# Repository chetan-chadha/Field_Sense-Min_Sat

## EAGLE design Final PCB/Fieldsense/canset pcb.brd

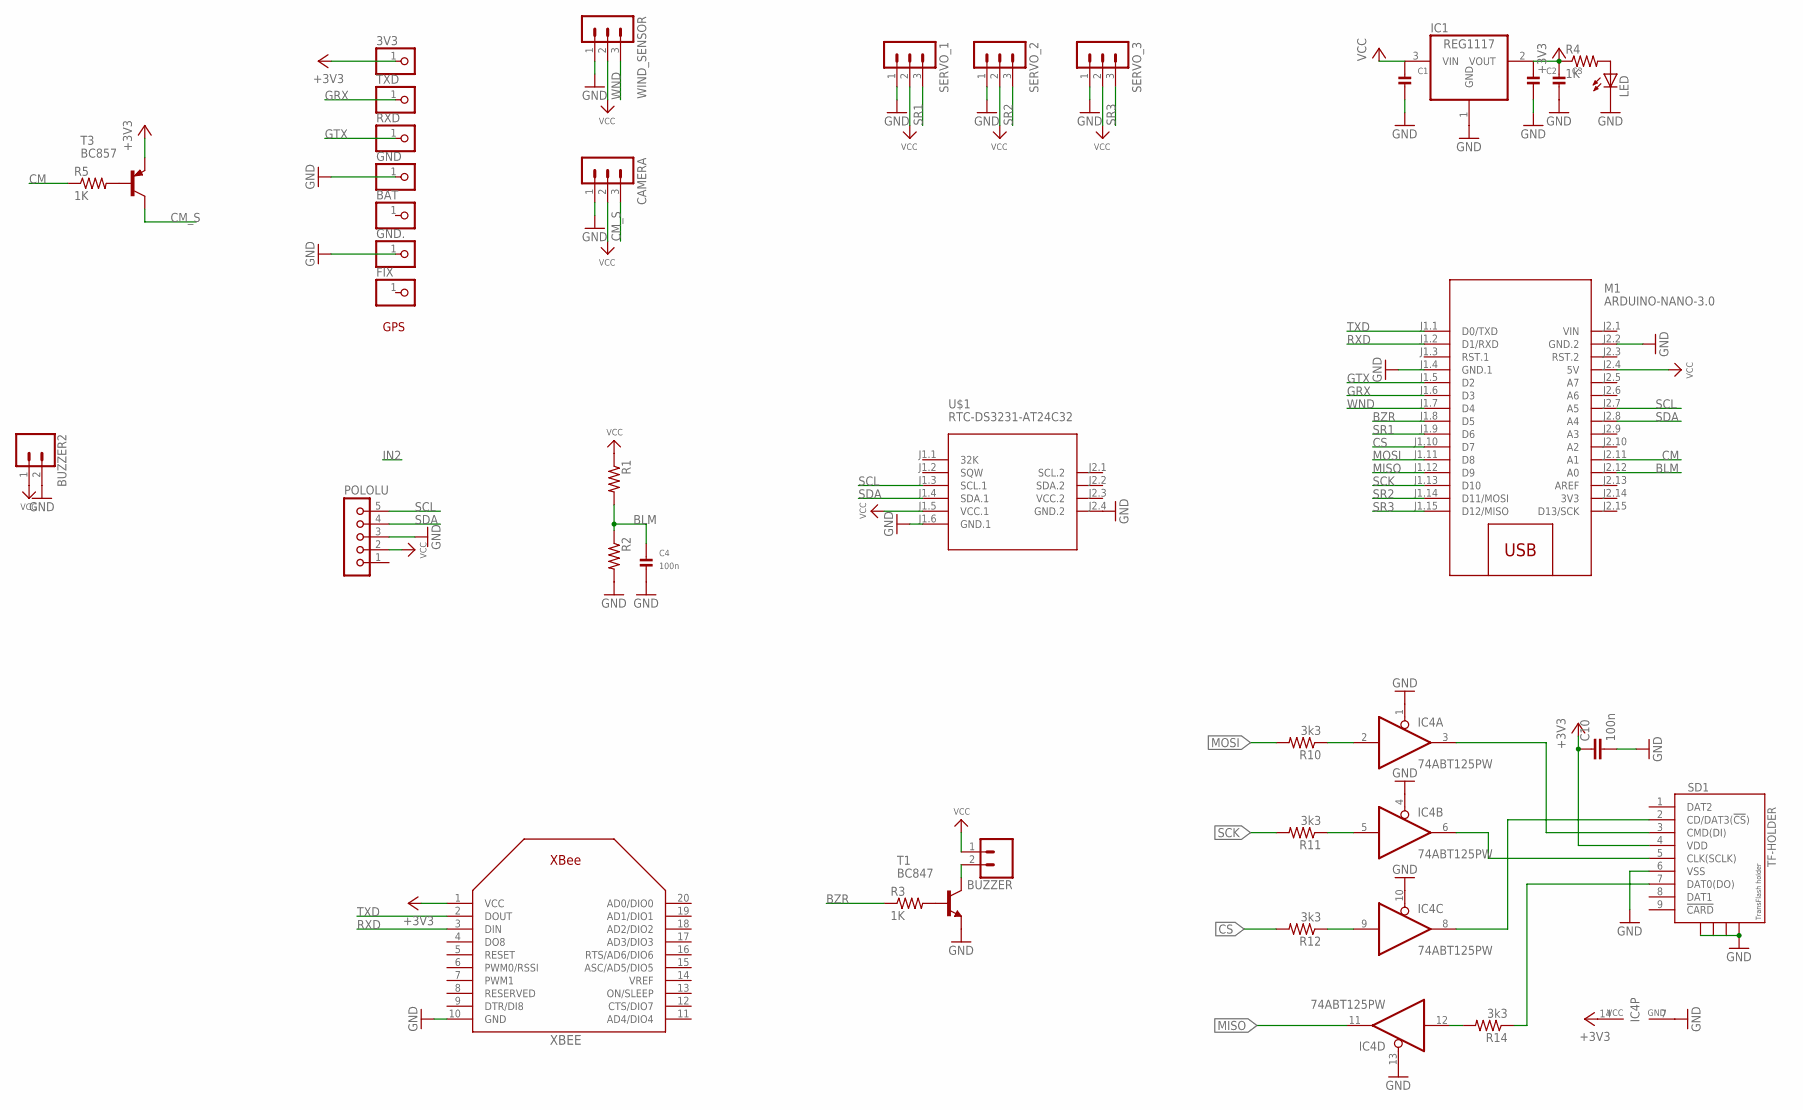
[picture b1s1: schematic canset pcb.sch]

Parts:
3V3: PINHD-1X1; 1X01
BAT: PINHD-1X1; 1X01
BUZZER, BUZZER2: CONN_02; 1X02
C1, C2, C3: CAP_CERAMIC_0805; _0805
C4: 100n; _0805
C10: 100n; C0603
CAMERA: MA03-1
FIX: PINHD-1X1; 1X01
GND, GND.: PINHD-1X1; 1X01
IC1: REG1117; SOT223
IC4: 74ABT125PW; TSSOP14
LED: LED5MM
M1: ARDUINO-NANO-3.0
POLOLU: JU05
R1, R2: R-US_M0805; M0805
R3, R4, R5: 1K; M0805
R10, R11, R12, R14: 3k3; R0603
RXD: PINHD-1X1; 1X01
SD1: TF-HOLDER; TF-PULL
SERVO_1, SERVO_2, SERVO_3: MA03-1
T1: BC847; SOT23
T3: BC857; SOT23
TXD: PINHD-1X1; 1X01
U$1: RTC-DS3231-AT24C32
WIND_SENSOR: MA03-1
XBEE: XBEE

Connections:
3V3: M1.J2.14 (3V3)
+3V3: 3V3.1, C2.1, C3.1, C10.1, IC1.2 (VOUT), IC4.14 (VCC), R4.1, SD1.4 (VDD), T3.2 (E), XBEE.1 (VCC)
BLM: C4.1, M1.J2.12 (A0), R1.2, R2.1
BZR: M1.J1.8 (D5), R3.1
CM: M1.J2.11 (A1), R5.1
CM_S: CAMERA.3, T3.3 (C)
CS: M1.J1.10 (D7), R12.2
GND: BUZZER2.2, C1.2, C2.2, C3.2, C4.2, C10.2, CAMERA.1, GND.1, GND..1, IC1.1 (GND), IC4.1 (OE), IC4.4 (OE), IC4.7 (GND), IC4.10 (OE), IC4.13 (OE), LED.K (C), M1.J1.4 (GND.1), M1.J2.2 (GND.2), POLOLU.3, R2.2, SD1.6 (VSS), SD1.S1, SD1.S2, SD1.S3, SD1.S4, SERVO_1.1, SERVO_2.1, SERVO_3.1, T1.2 (E), U$1.J1.6 (GND.1), U$1.J2.4 (GND.2), WIND_SENSOR.1, XBEE.10 (GND)
GRX: M1.J1.6 (D3), TXD.1
GTX: M1.J1.5 (D2), RXD.1
MISO: IC4.11 (O), M1.J1.12 (D9)
MOSI: M1.J1.11 (D8), R10.2
unnamed: R3.2, T1.1 (B)
unnamed: BUZZER.2, T1.3 (C)
unnamed: LED.A, R4.2
unnamed: R5.2, T3.1 (B)
unnamed: IC4.12 (I), R14.2
unnamed: IC4.2 (I), R10.1
unnamed: IC4.5 (I), R11.1
unnamed: IC4.9 (I), R12.1
unnamed: IC4.3 (O), SD1.3 (CMD(DI))
unnamed: R14.1, SD1.7 (DAT0(DO))
unnamed: IC4.8 (O), SD1.2 (CD/DAT3(!CS!))
unnamed: IC4.6 (O), SD1.5 (CLK(SCLK))
RXD: M1.J1.2 (D1/RXD), XBEE.3 (DIN)
SCK: M1.J1.13 (D10), R11.2
SCL: M1.J2.7 (A5), POLOLU.5, U$1.J1.3 (SCL.1)
SDA: M1.J2.8 (A4), POLOLU.4, U$1.J1.4 (SDA.1)
SR1: M1.J1.9 (D6), SERVO_1.3
SR2: M1.J1.14 (D11/MOSI), SERVO_2.3
SR3: M1.J1.15 (D12/MISO), SERVO_3.3
TXD: M1.J1.1 (D0/TXD), XBEE.2 (DOUT)
VCC: BUZZER.1, BUZZER2.1, C1.1, CAMERA.2, IC1.3 (VIN), M1.J2.4 (5V), POLOLU.2, R1.1, SERVO_1.2, SERVO_2.2, SERVO_3.2, U$1.J1.5 (VCC.1), WIND_SENSOR.2
VCC.2: U$1.J2.3 (VCC.2)
VIN: M1.J2.1 (VIN)
WND: M1.J1.7 (D4), WIND_SENSOR.3

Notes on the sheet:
GPS

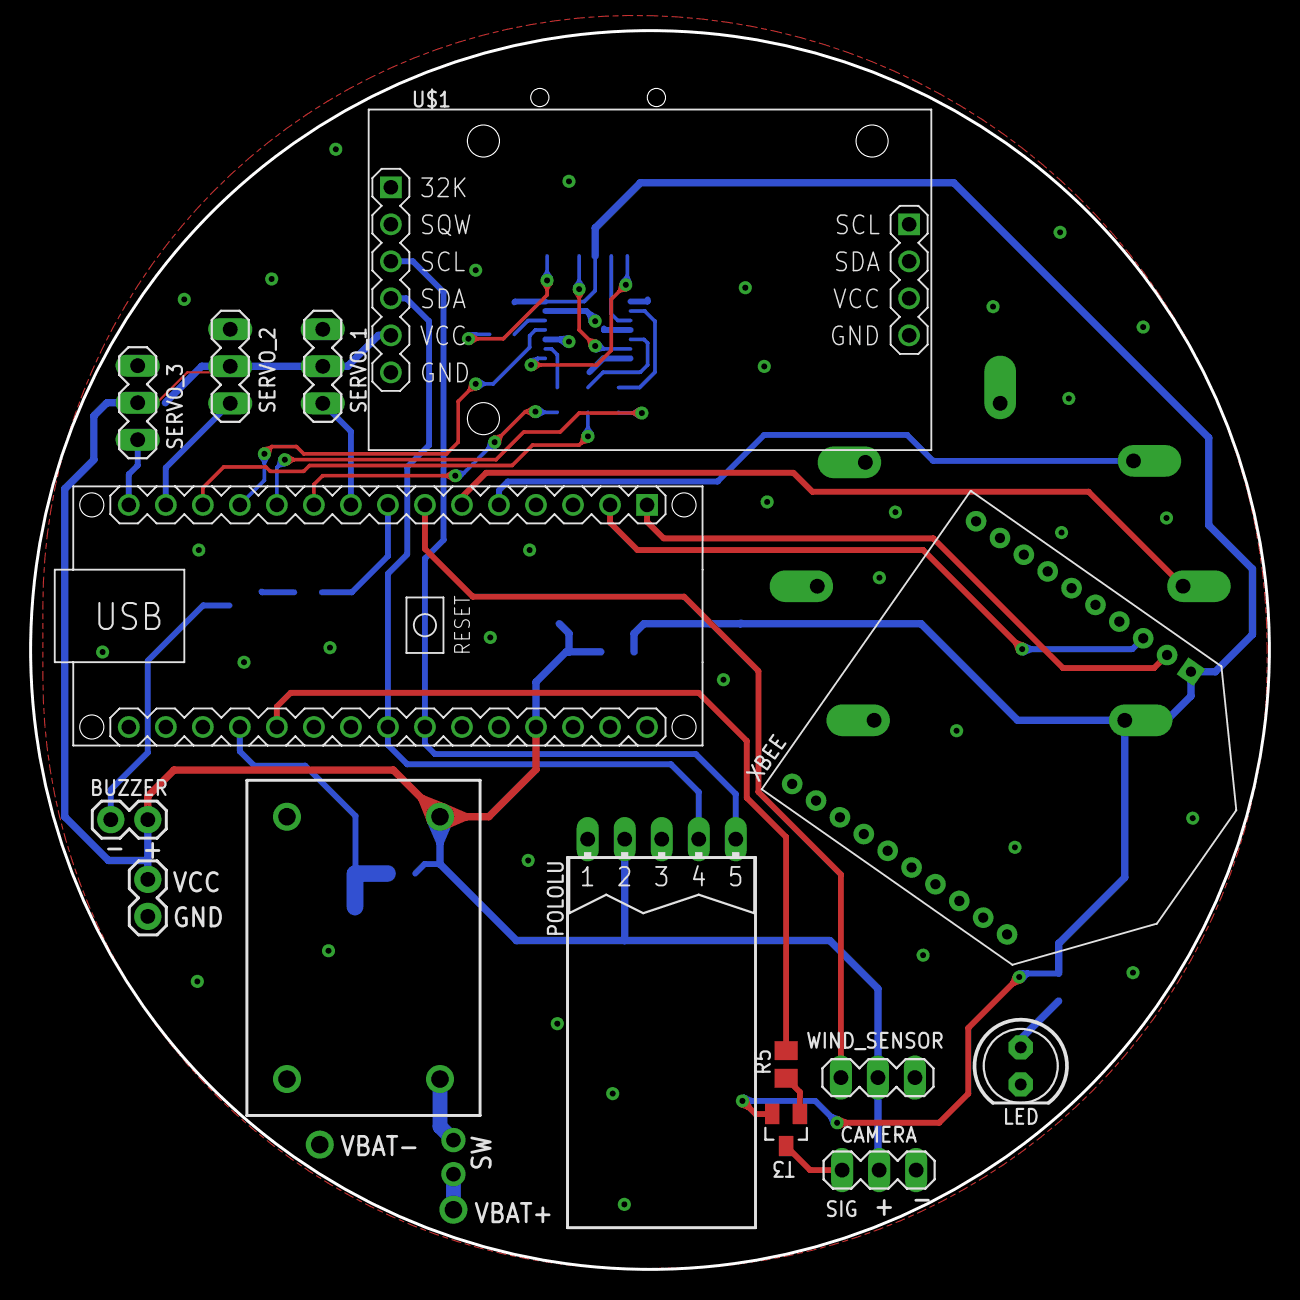
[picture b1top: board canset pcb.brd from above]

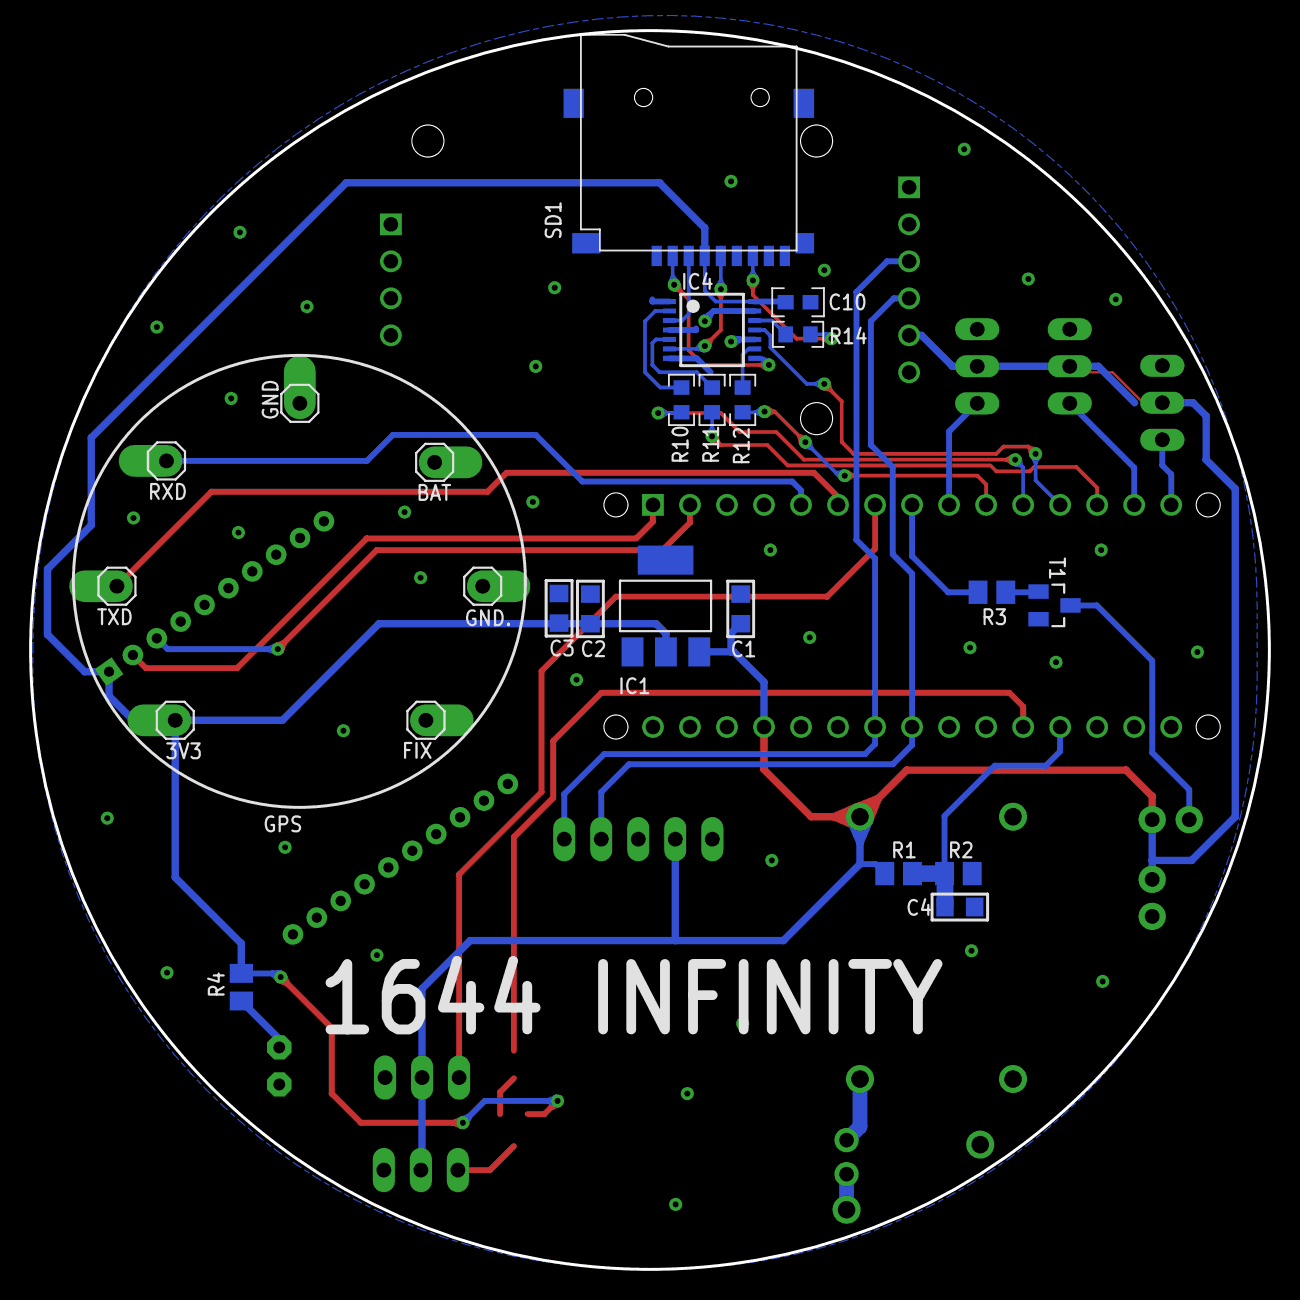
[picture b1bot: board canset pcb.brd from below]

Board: 2 copper layers, 85.0 x 85.0 mm, 38 parts (24 on the bottom side), 33 nets.

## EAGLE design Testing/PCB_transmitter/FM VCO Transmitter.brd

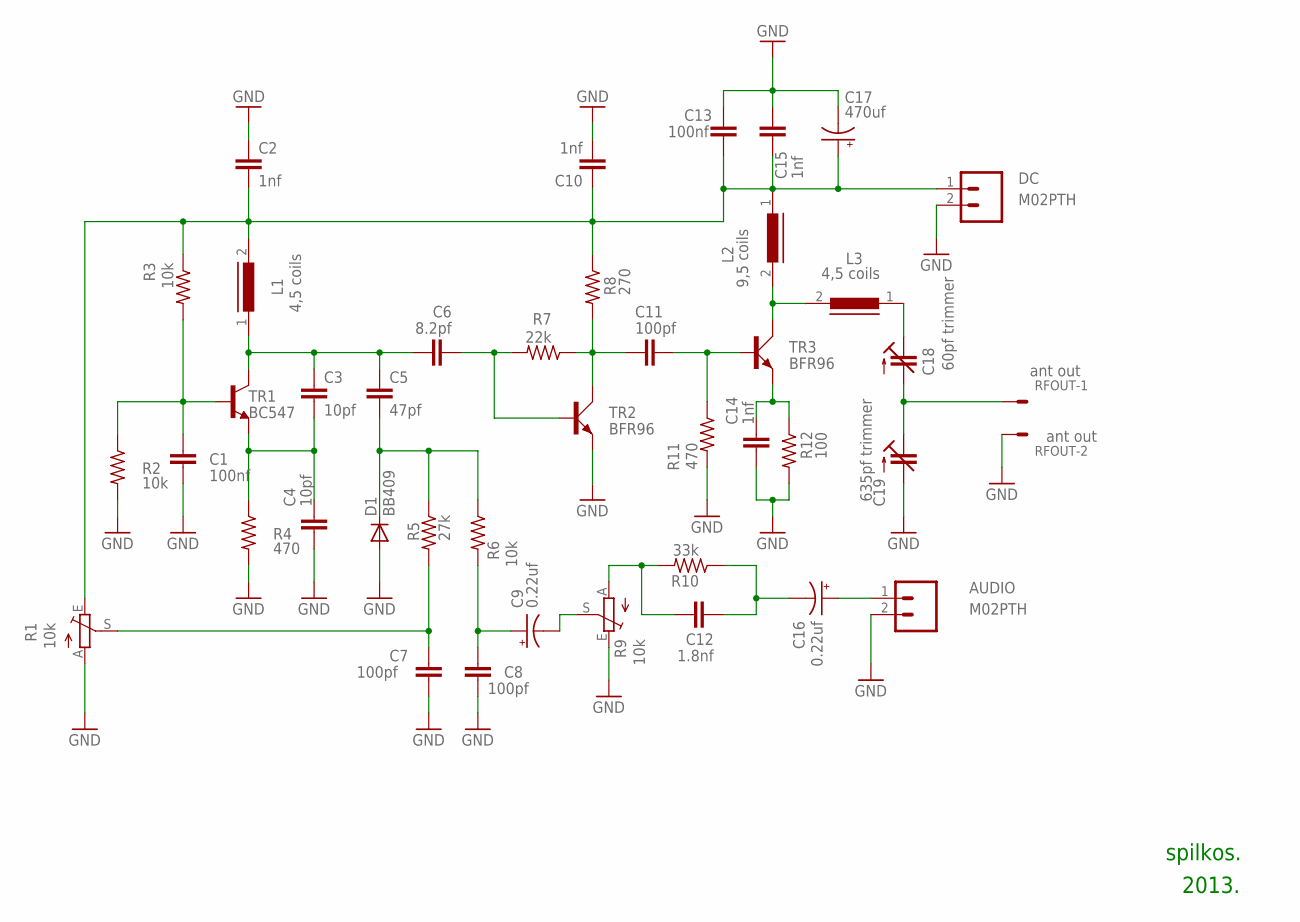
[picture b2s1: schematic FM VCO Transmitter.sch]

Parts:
AUDIO: M02PTH; 1X02
C1, C13: 100nf; C025-024X044
C2, C10, C14, C15: 1nf; C025-024X044
C3, C4: 10pf; C025-024X044
C5: 47pf; C025-024X044
C6: 8.2pf; C025-024X044
C7, C8, C11: 100pf; C025-024X044
C9, C16: 0.22uf; E2,5-6E
C12: 1.8nf; C025-024X044
C17: 470uf; E2,5-6E
C18: 60pf trimmer; CTRIMTZ03
C19: 635pf trimmer; CTRIMTZ03
D1: BB409; DO35-10
DC: M02PTH; 1X02
L1, L3: 4,5 coils; 82114R
L2: 9,5 coils; 82114R
R1, R9: 10k; B25P
R2, R3, R6: 10k; 0309V
R4, R11: 470; 0309V
R5: 27k; 0309V
R7: 22k; 0309V
R8: 270; 0309V
R10: 33k; 0309V
R12: 100; 0309V
RFOUT: ant out; 332-02
TR1: BC547; TO92
TR2, TR3: BFR96; SOT37

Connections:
GND: AUDIO.2, C1.2, C2.1, C4.2, C7.2, C8.2, C10.2, C13.1, C14.2, C15.1, C17.-, C19.2 (A), D1.A, DC.2, R1.A, R2.2, R4.2, R9.E, R11.2, R12.2, RFOUT.2, TR2.2 (E)
unnamed: C3.2, C4.1, R4.1, TR1.1 (E)
unnamed: C7.1, R1.S, R5.2
unnamed: C1.1, R2.1, R3.2, TR1.2 (B)
unnamed: C8.1, C9.+, R6.2
unnamed: C11.1, R7.1, R8.2, TR2.1 (C)
unnamed: C9.-, R9.S
unnamed: C12.1, R9.A, R10.2
unnamed: C12.2, C16.-, R10.1
unnamed: C14.1, R12.1, TR3.2 (E)
unnamed: L2.2, L3.2, TR3.1 (C)
unnamed: C18.1 (E), L3.1
unnamed: C18.2 (A), C19.1 (E), RFOUT.1
unnamed: AUDIO.1, C16.+
WIRE_1: C3.1, C5.1, C6.1, L1.1, TR1.3 (C)
WIRE_2: C5.2, D1.C, R5.1, R6.1
WIRE_3: C6.2, R7.2, TR2.3 (B)
WIRE_4: C2.2, C10.1, C13.2, C15.2, C17.+, DC.1, L1.2, L2.1, R1.E, R3.1, R8.1
WIRE_5: C11.2, R11.1, TR3.3 (B)

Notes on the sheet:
spilkos.
2013.

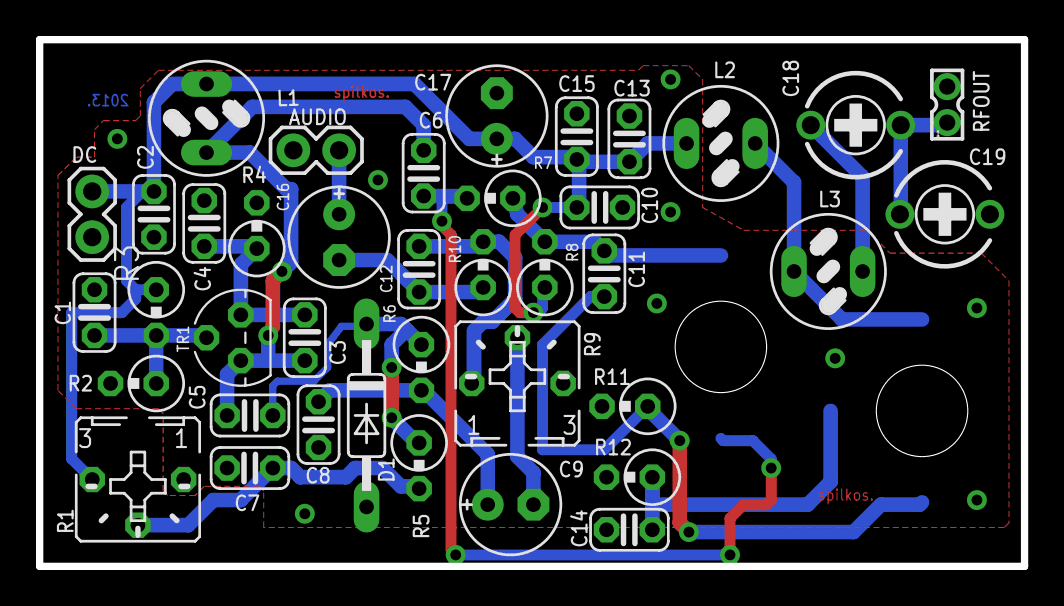
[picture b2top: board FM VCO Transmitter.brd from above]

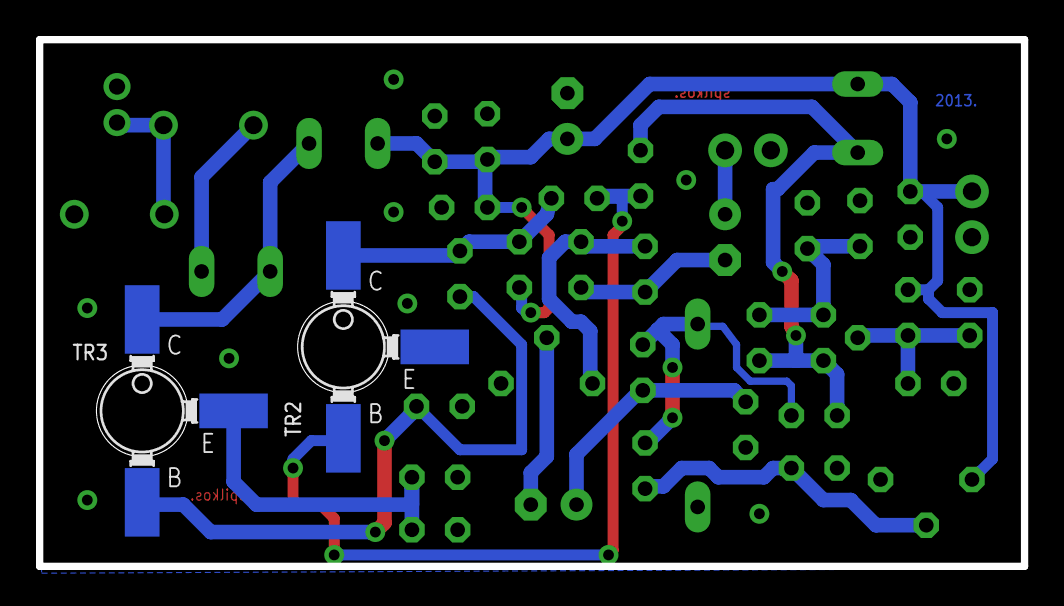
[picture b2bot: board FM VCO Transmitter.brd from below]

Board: 2 copper layers, 54.7 x 29.3 mm, 41 parts (2 on the bottom side), 19 nets.

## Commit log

2018-09-15 Final Commit

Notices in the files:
parts and their libraries:
diy-modules: Released under the Creative Commons Attribution 4.0 International License: http://creativecommons.org/licenses/by/4.0
microbuilder: This work is placed in the public domain, and may be freely used for commercial and non-commercial work with the following conditions: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
